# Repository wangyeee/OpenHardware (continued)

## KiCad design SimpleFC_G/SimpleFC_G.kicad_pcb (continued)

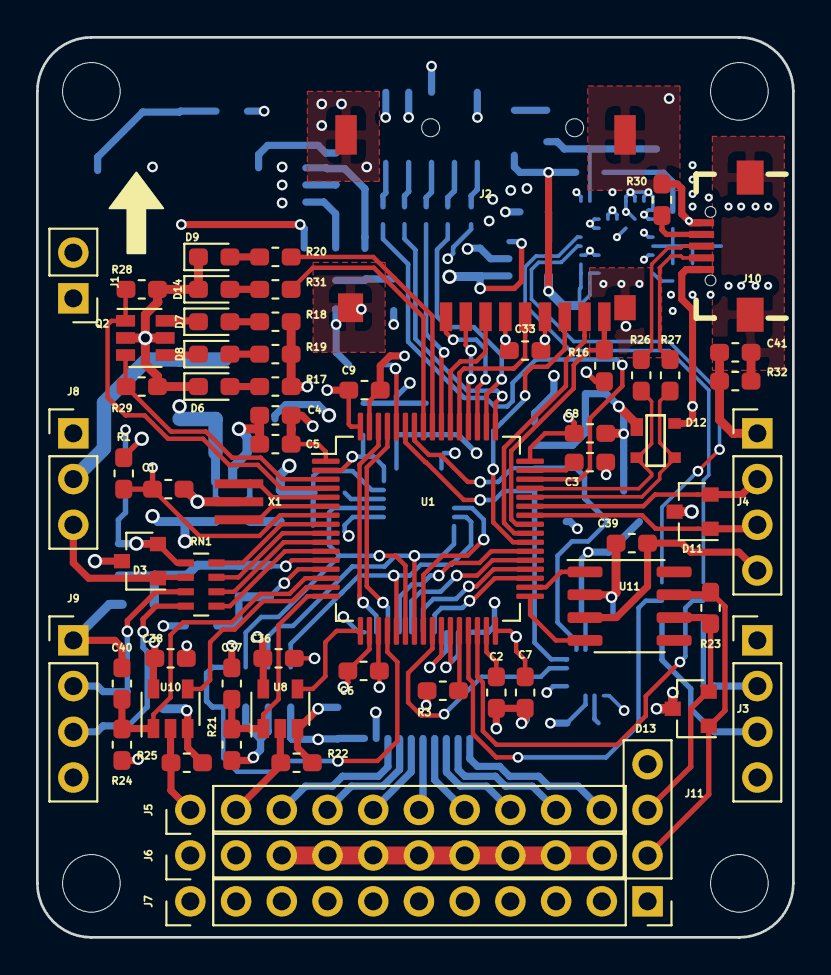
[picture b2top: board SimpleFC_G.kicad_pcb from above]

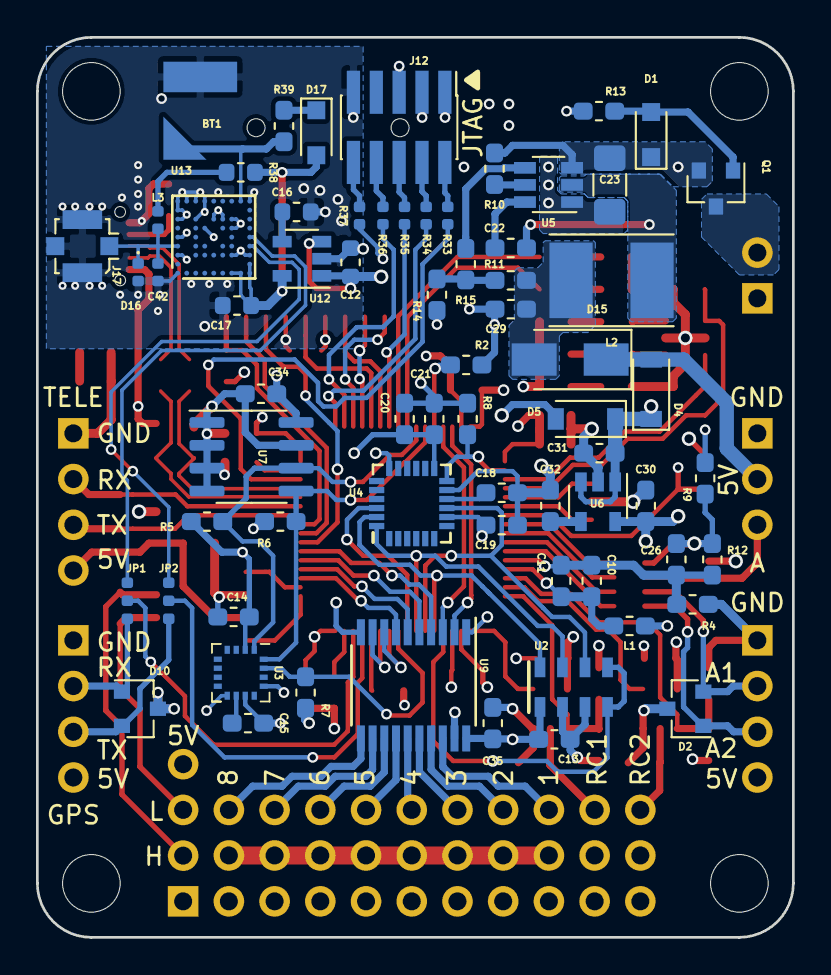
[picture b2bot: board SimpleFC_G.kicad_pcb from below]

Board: 4 copper layers, 42.0 x 50.0 mm, 134 parts (68 on the bottom side), 117 nets.

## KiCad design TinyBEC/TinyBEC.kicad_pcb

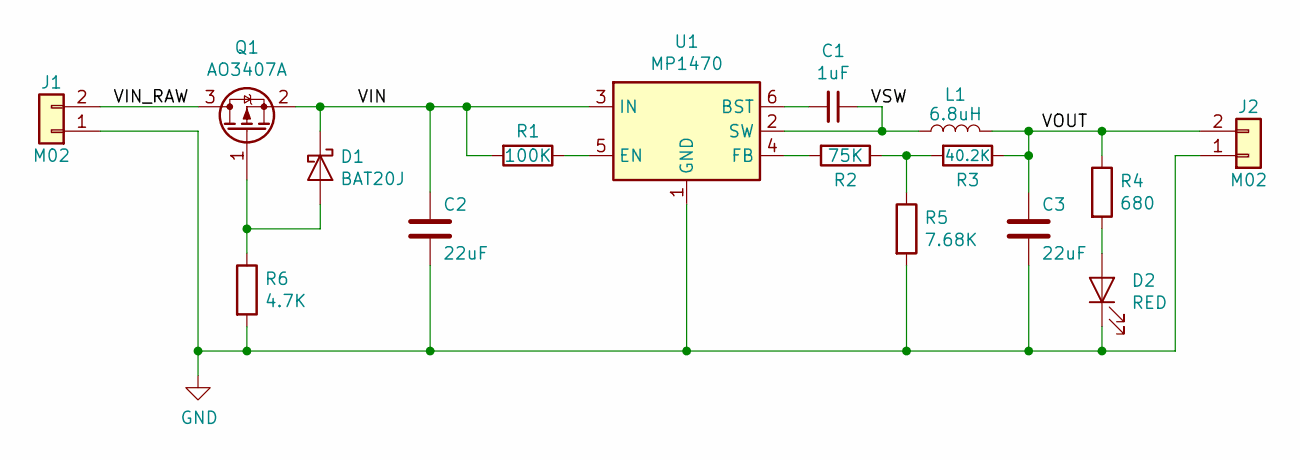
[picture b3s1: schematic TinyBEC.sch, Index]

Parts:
C1: 1uF; C_0603_1608Metric_Pad1.05x0.95mm_HandSolder
C2: 22uF; C_1812_4532Metric_Pad1.30x3.40mm_HandSolder
C3: 22uF; C_0805_2012Metric_Pad1.15x1.40mm_HandSolder
D1: BAT20J; D_SOD-123
D2: RED; LED_0603_1608Metric_Castellated
J1, J2: M02; PinHeader_1x02_P2.54mm_Vertical
L1: 6.8uH; L_Taiyo-Yuden_NR-50xx_HandSoldering
Q1: AO3407A; SOT-23
R1: 100K; R_0603_1608Metric_Pad1.05x0.95mm_HandSolder
R2: 75K; R_0603_1608Metric_Pad1.05x0.95mm_HandSolder
R3: 40.2K; R_0603_1608Metric_Pad1.05x0.95mm_HandSolder
R4: 680; R_0603_1608Metric_Pad1.05x0.95mm_HandSolder
R5: 7.68K; R_0603_1608Metric_Pad1.05x0.95mm_HandSolder
R6: 4.7K; R_0603_1608Metric_Pad1.05x0.95mm_HandSolder
U1: MP1470; TSOT-23-6

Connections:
/VIN: C2.1, D1.1 (K), Q1.2 (S), R1.2, U1.3 (IN)
/VIN_RAW: J1.2, Q1.3 (D)
/VOUT: C3.1, J2.2, L1.2, R3.1, R4.1
/VSW: C1.1, L1.1, U1.2 (SW)
GND: C2.2, C3.2, D2.1 (K), J1.1, J2.1, R5.2, R6.2, U1.1 (GND)
unnamed: C1.2, U1.6 (BST)
unnamed: D1.2 (A), Q1.1 (G), R6.1
unnamed: D2.2 (A), R4.2
unnamed: R1.1, U1.5 (EN)
unnamed: R2.1, R3.2, R5.1
unnamed: R2.2, U1.4 (FB)

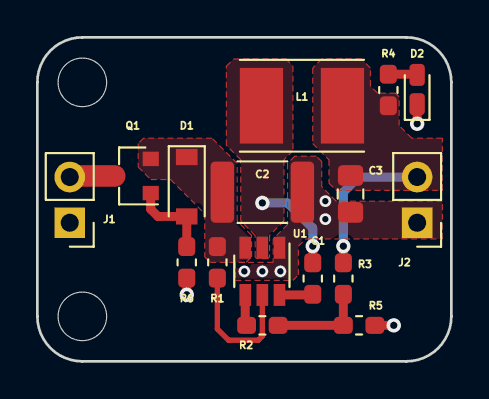
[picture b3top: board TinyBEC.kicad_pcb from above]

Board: 2 copper layers, 23.0 x 18.0 mm, 16 parts (0 on the bottom side), 11 nets.

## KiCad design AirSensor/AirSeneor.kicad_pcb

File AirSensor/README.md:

# Air Speed/Pressure Sensor
A barometer and differential pressure sensor board with CAN bus.

***WARNING: The PCB design has not been fabricated, Use with caution!***

## Hardware Design
### Main Components
1. [MS4525DO](https://www.te.com/usa-en/product-CAT-BLPS0002.html) differential pressure sensor.
2. [MS5611](https://www.te.com/usa-en/product-CAT-BLPS0036.html) air pressure sensor.
3. [STM32F072](https://www.st.com/en/microcontrollers-microprocessors/stm32f072cb.html) MCU.
4. [TJA1050](https://www.nxp.com/products/analog/interfaces/in-vehicle-network/can-transceiver-and-controllers/high-speed-can-transceiver:TJA1050) CAN bus transceiver.

## Software
The software is still work in progress. The following functionalities will be implemented.

1. Drivers barometer, differential pressure sensor and CAN bus.
2. Application layer supporting for [UAVCAN](https://uavcan.org/) protocol.

## 3D rendering

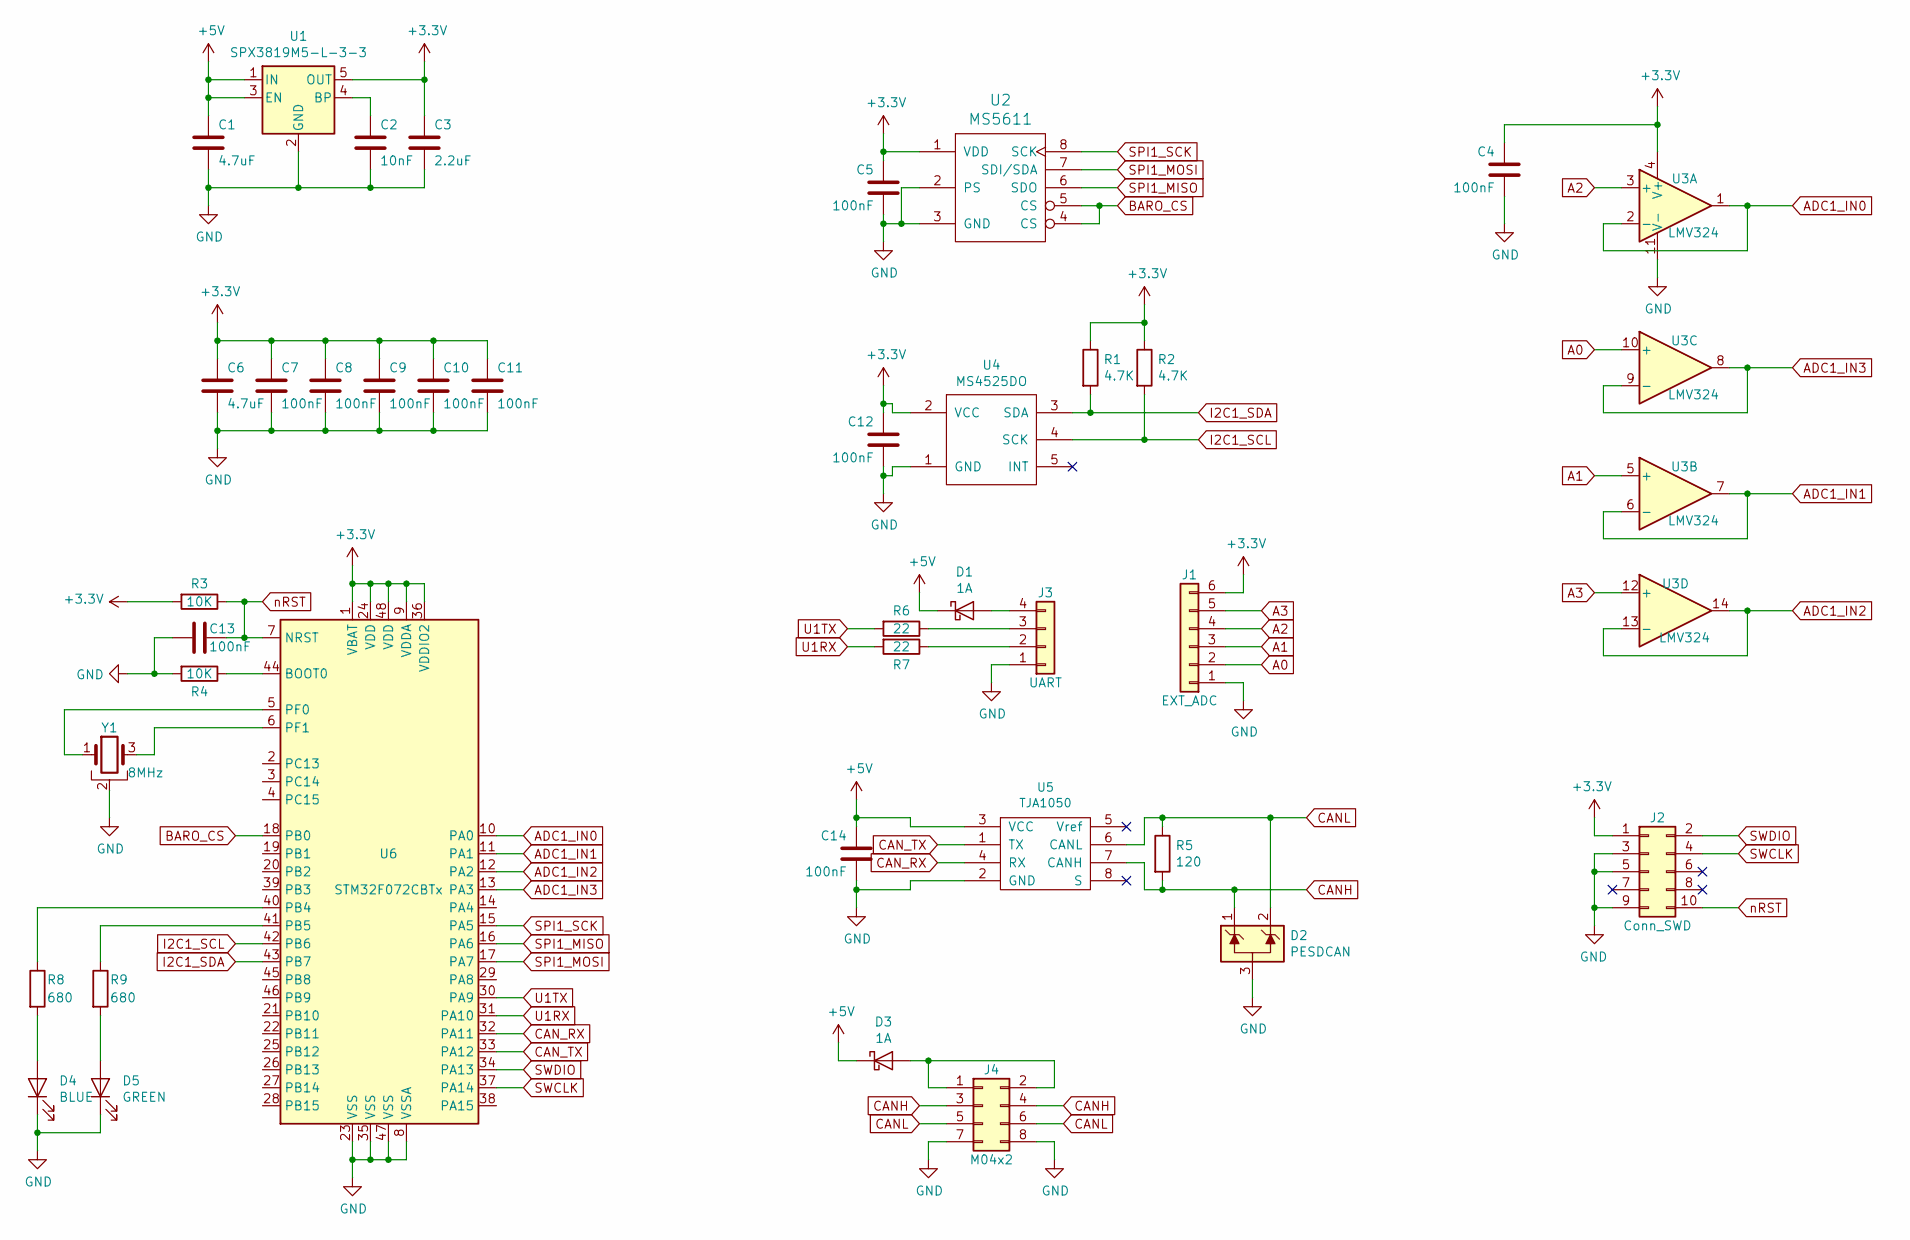
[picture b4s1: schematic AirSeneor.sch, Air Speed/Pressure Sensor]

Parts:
C1, C6: 4.7uF; C_0603_1608Metric
C2: 10nF; C_0603_1608Metric
C3: 2.2uF; C_0603_1608Metric
C4, C5, C7, C8, C9, C10, C11, C12, C13, C14: 100nF; C_0603_1608Metric
D1, D3: 1A; D_SOD-123
D2: PESDCAN; SOT-23
D4: BLUE; LED_0603_1608Metric
D5: GREEN; LED_0603_1608Metric
J1: EXT_ADC; PinHeader_1x06_P2.00mm_Vertical
J2: Conn_SWD; PinHeader_2x05_P1.27mm_Vertical_SMD
J3: UART; PinHeader_1x04_P2.54mm_Vertical
J4: M04x2; PinHeader_2x04_P2.54mm_Horizontal
R1, R2: 4.7K; R_0603_1608Metric
R3, R4: 10K; R_0603_1608Metric
R5: 120; R_0603_1608Metric
R6, R7: 22; R_0603_1608Metric
R8, R9: 680; R_0603_1608Metric
U1: SPX3819M5-L-3-3; SOT-23-5
U2: MS5611; LGA-8_3x5mm_P1.25mm
U3: LMV324; SOIC-14_3.9x8.7mm_P1.27mm
U4: MS4525DO; MS4525DO-DS
U5: TJA1050; SOIC-8_3.9x4.9mm_P1.27mm
U6: STM32F072CBTx; LQFP-48_7x7mm_P0.5mm
Y1: 8MHz; CERALOCK-CSTCE

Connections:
+3V3: C3.1, C4.1, C5.1, C6.1, C7.1, C8.1, C9.1, C10.1, C11.1, C12.1, J1.6, J2.1, R1.1, R2.1, R3.2, U1.5 (OUT), U2.1 (VDD), U3.4 (V+), U4.2 (VCC), U6.1 (VBAT), U6.9 (VDDA), U6.24 (VDD), U6.36 (VDDIO2), U6.48 (VDD)
+5V: C1.1, C14.1, D1.1 (K), D3.1 (K), U1.1 (IN), U1.3 (EN), U5.3 (VCC)
A0: J1.2, U3.10 (+)
A1: J1.3, U3.5 (+)
A2: J1.4, U3.3 (+)
A3: J1.5, U3.12 (+)
ADC1_IN0: U3.1, U3.2 (-), U6.10 (PA0)
ADC1_IN1: U3.6 (-), U3.7, U6.11 (PA1)
ADC1_IN2: U3.13 (-), U3.14, U6.12 (PA2)
ADC1_IN3: U3.8, U3.9 (-), U6.13 (PA3)
BARO_CS: U2.4 (CS), U2.5 (CS), U6.18 (PB0)
CANH: D2.1 (K), J4.3, J4.4, R5.2, U5.7 (CANH)
CANL: D2.2 (K), J4.5, J4.6, R5.1, U5.6 (CANL)
CAN_RX: U5.4 (RX), U6.32 (PA11)
CAN_TX: U5.1 (TX), U6.33 (PA12)
GND: C1.2, C2.2, C3.2, C4.2, C5.2, C6.2, C7.2, C8.2, C9.2, C10.2, C11.2, C12.2, C13.2, C14.2, D2.3 (A), D4.1 (K), D5.1 (K), J1.1, J2.3, J2.5, J2.9, J3.1, J4.7, J4.8, R4.2, U1.2 (GND), U2.2 (PS), U2.3 (GND), U3.11 (V-), U4.1 (GND), U5.2 (GND), U6.8 (VSSA), U6.23 (VSS), U6.35 (VSS), U6.47 (VSS), Y1.2
I2C1_SCL: R2.2, U4.4 (SCK), U6.42 (PB6)
I2C1_SDA: R1.2, U4.3 (SDA), U6.43 (PB7)
unnamed: C2.1, U1.4 (BP)
unnamed: D1.2 (A), J3.4
unnamed: D3.2 (A), J4.1, J4.2
unnamed: D4.2 (A), R8.2
unnamed: D5.2 (A), R9.2
unnamed: J3.2, R7.1
unnamed: J3.3, R6.1
unnamed: R4.1, U6.44 (BOOT0)
unnamed: R8.1, U6.40 (PB4)
unnamed: R9.1, U6.41 (PB5)
unnamed: U6.5 (PF0), Y1.1
unnamed: U6.6 (PF1), Y1.3
SPI1_MISO: U2.6 (SDO), U6.16 (PA6)
SPI1_MOSI: U2.7 (SDI/SDA), U6.17 (PA7)
SPI1_SCK: U2.8 (SCK), U6.15 (PA5)
SWCLK: J2.4, U6.37 (PA14)
SWDIO: J2.2, U6.34 (PA13)
U1RX: R7.2, U6.31 (PA10)
U1TX: R6.2, U6.30 (PA9)
nRST: C13.1, J2.10, R3.1, U6.7 (NRST)

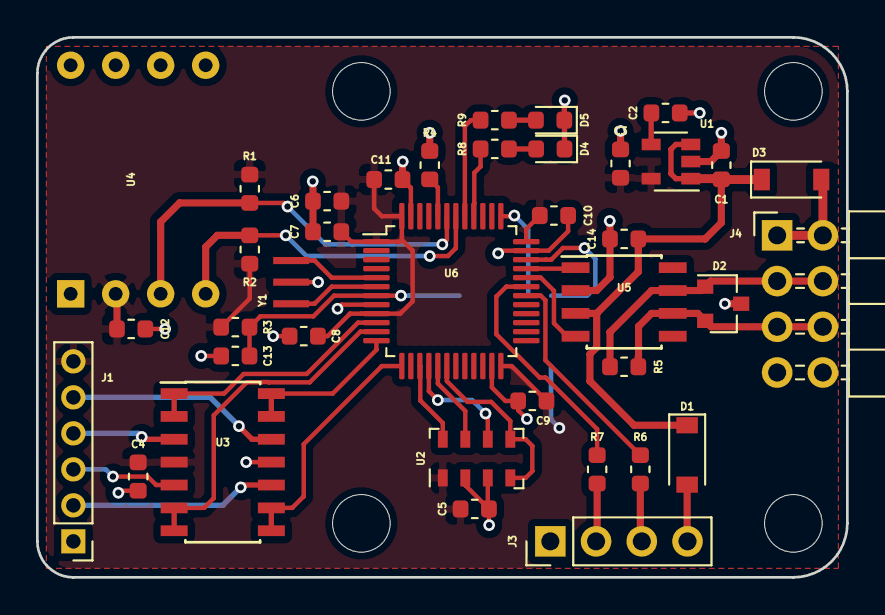
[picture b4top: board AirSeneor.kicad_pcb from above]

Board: 2 copper layers, 45.0 x 30.0 mm, 39 parts (1 on the bottom side), 38 nets.

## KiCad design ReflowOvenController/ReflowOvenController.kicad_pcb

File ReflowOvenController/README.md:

# Reflow Oven Controller
A reflow oven controller derived from [0xPIT/reflowOvenController](https://github.com/0xPIT/reflowOvenController).

**Warning: Lethal mains voltage is connected to the PCB, extreme care must be taken for the whole time. Seek help from professional technicians whenever possible.**

I decide to design my own board mainly because the solid state relay used in the original project is obsolete. In order to avoid this, I use a triac and an optocoupler to build a solid state relay. It's much easier to find alternatives for discrete components than integrate ones.

Another change from the original design is using ATmega328P to replace ATmega32U4 used in Arduino Pro Micro, this is simply because I already have some ATmega328P chips available. Note that due to this change, the Timer3 library is not available on this hardware.

### 3D preview

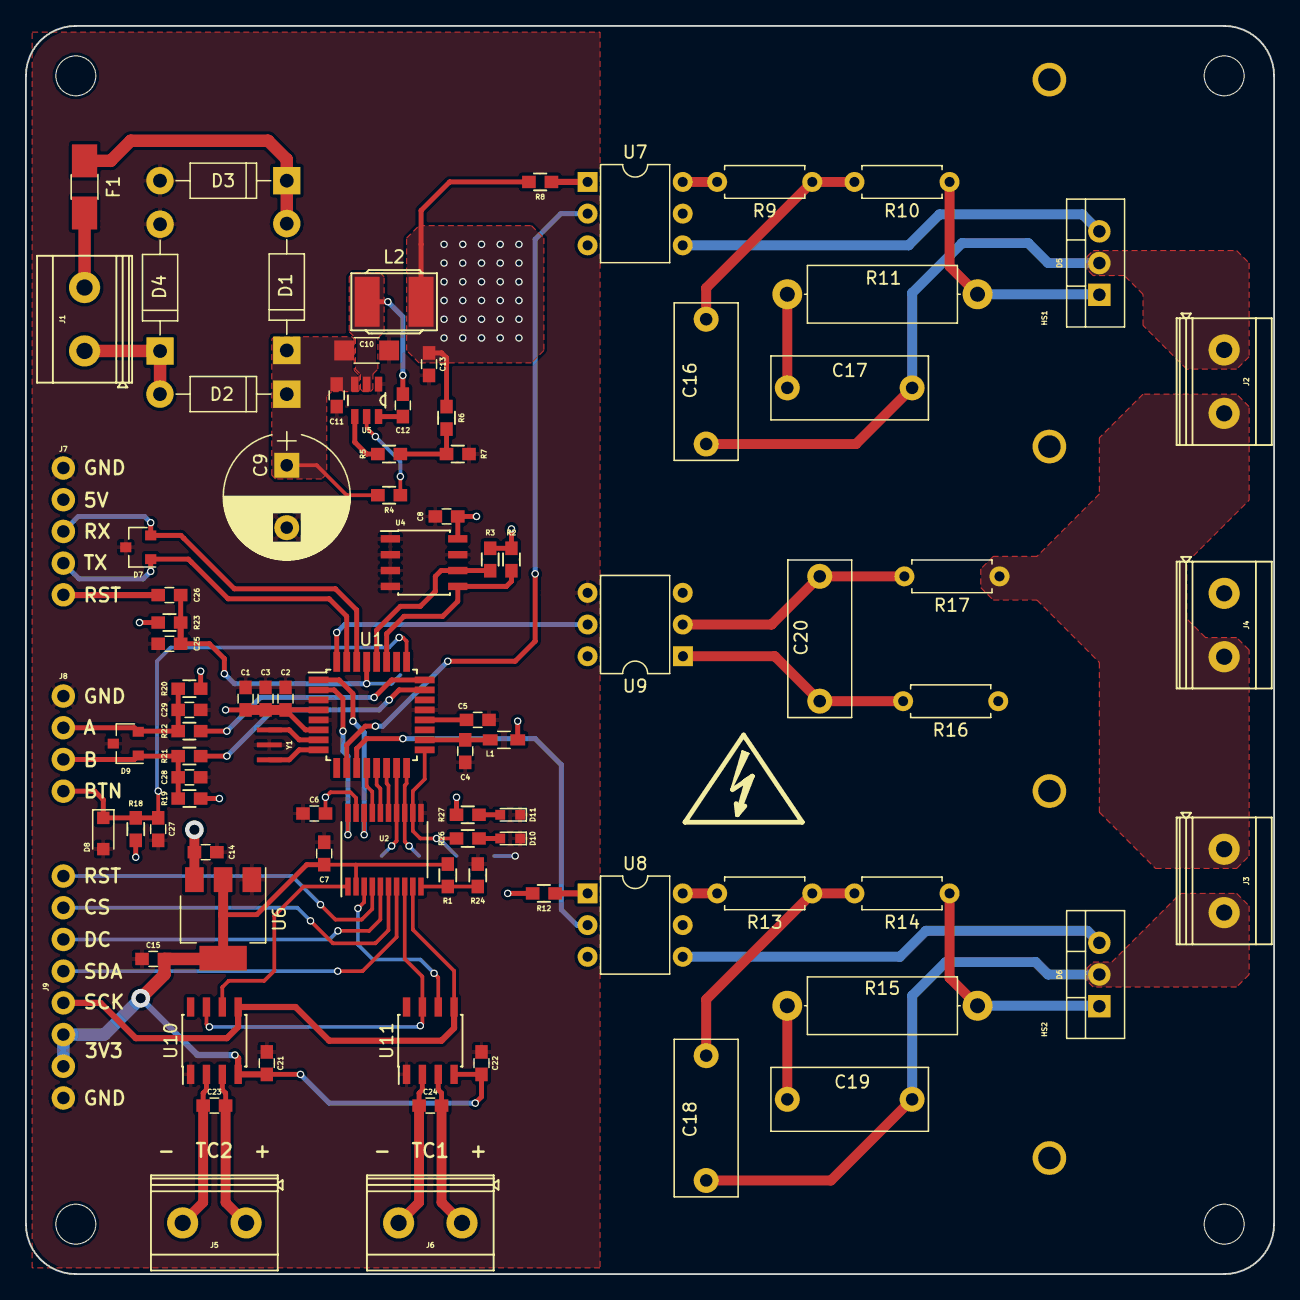
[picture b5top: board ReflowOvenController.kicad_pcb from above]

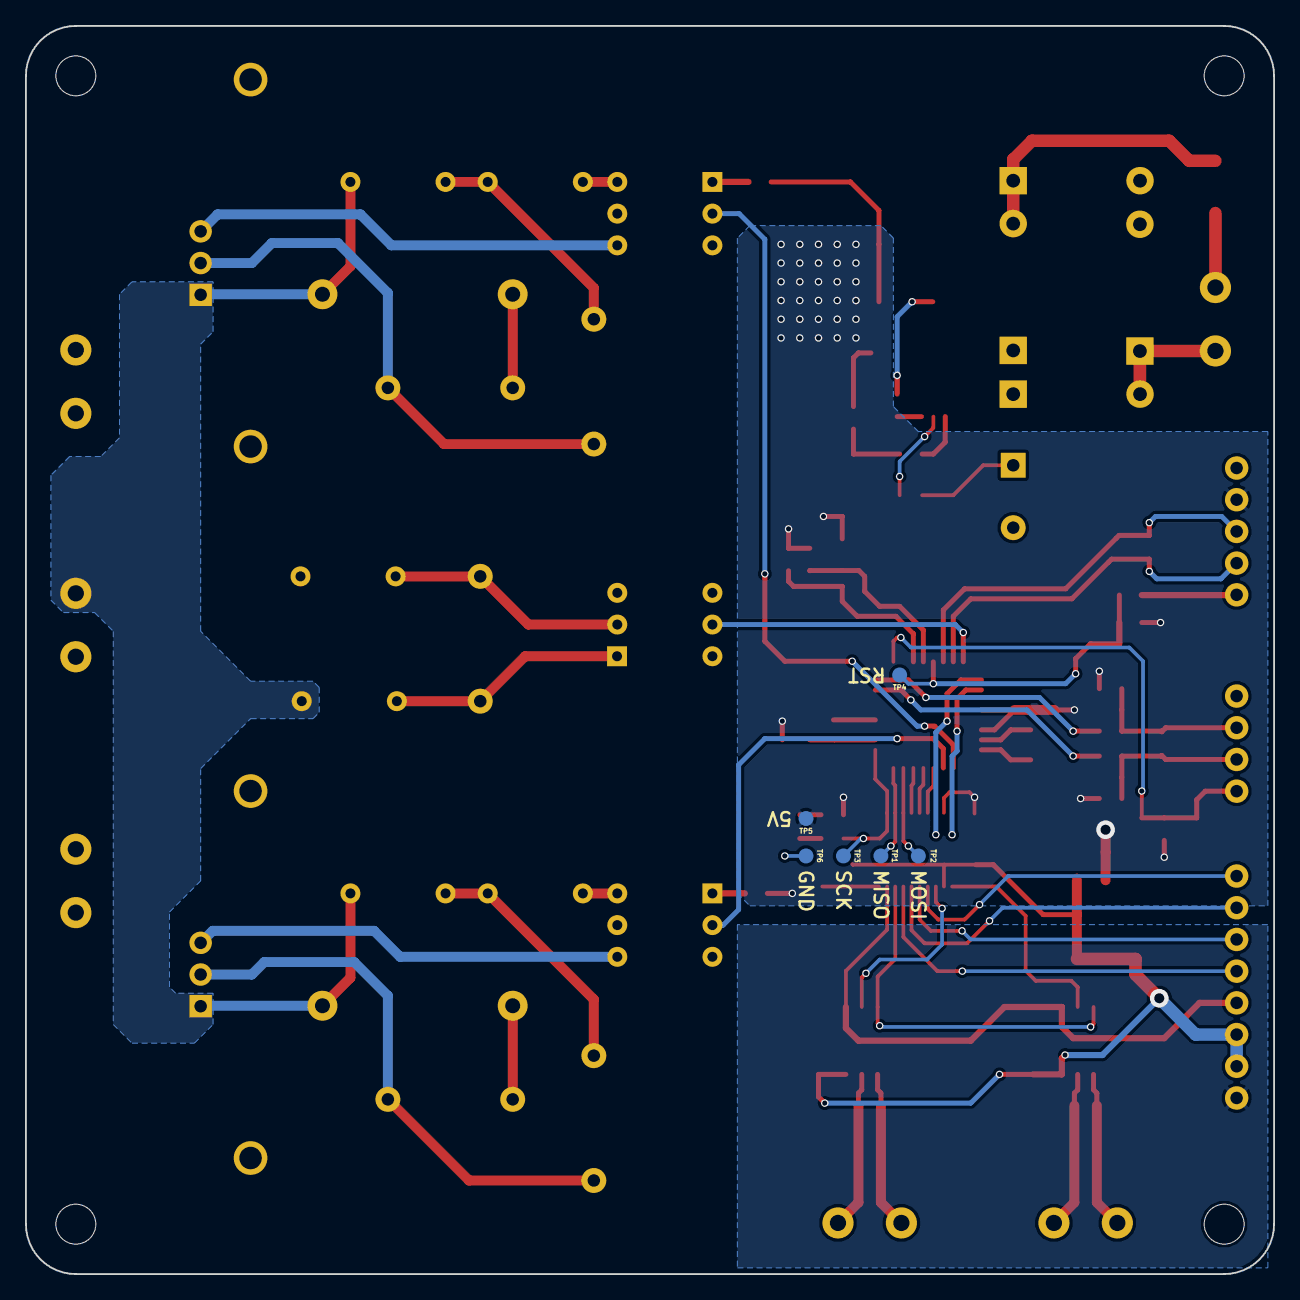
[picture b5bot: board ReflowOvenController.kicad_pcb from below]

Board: 2 copper layers, 100.0 x 100.0 mm, 102 parts (6 on the bottom side), 69 nets.

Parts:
C1: 4.7uF; C_0603_HandSoldering
C2, C3, C4, C5, C6, C7, C8, C11, C21, C22: 100nF; C_0603_HandSoldering
C9: 470uF; CP_Radial_D10.0mm_P5.00mm
C10: 22uF; C_1206_HandSoldering
C12, C14, C15: 1uF; C_0603_HandSoldering
C13: 22uF; C_0603_HandSoldering
C16, C18: 50nF; C_Disc_D12.5mm_W5.0mm_P10.00mm
C17, C19: 10nF; C_Disc_D12.5mm_W5.0mm_P10.00mm
C20: 100nF; C_Disc_D12.5mm_W5.0mm_P10.00mm
C23, C24, C27, C28, C29: 10nF; C_0603_HandSoldering
C25: NC; C_0603_HandSoldering
C26: 4.7nF; C_0603_HandSoldering
D1, D2, D3, D4: 1N4001; D_DO-41_SOD81_P10.16mm_Horizontal
D5, D6: BTA16; TO-220_Vertical
D7, D9: PESD5V; SOT-23
D8: PESD5V; D_SOD-323_HandSoldering
D10: GREEN; LED_0603
D11: RED; LED_0603
F1: 1A; Fuse_SMD1206_HandSoldering
HS1, HS2: XSD1226-362
HV: Symbol_HighVoltage_Type2_SlikTop_VerySmall; Symbol_HighVoltage_Type2_SilkTop_VerySmall
J1, J5, J6: CONN_01X02; MKDS3-2-5.08
J2: HEATER; MKDS3-2-5.08
J3: FAN; MKDS3-2-5.08
J4: MAIN; MKDS3-2-5.08
J7: M05
J8: M04
J9: M08
L1: 1K; L_0603_HandSoldering
L2: 6.8uH; Choke_SMD_Taiyo_NRS50XX-Handsoldering
M1, M2, M3, M4: M3; MountingHole_3.2mm_M3
R1, R2, R3: 4.7K; R_0603_HandSoldering
R4: 100K; R_0603_HandSoldering
R5: 75K; R_0603_HandSoldering
R6: 40.2K; R_0603_HandSoldering
R7: 7.68K; R_0603_HandSoldering
R8, R12, R21, R22: 100; R_0603_HandSoldering
R9, R13: 360; R_Axial_DIN0207_L6.3mm_D2.5mm_P7.62mm_Horizontal
R10, R14: 470; R_Axial_DIN0207_L6.3mm_D2.5mm_P7.62mm_Horizontal
R11, R15: 39; R_Axial_DIN0414_L11.9mm_D4.5mm_P15.24mm_Horizontal
R16, R17: 47K; R_Axial_DIN0207_L6.3mm_D2.5mm_P7.62mm_Horizontal
R18, R19, R20, R23: 10K; R_0603_HandSoldering
R24: NC; R_0603_HandSoldering
R26, R27: 330; R_0603_HandSoldering
TP1, TP2, TP3, TP4, TP5, TP6: TEST; TESTPAD_SMALL
U1: ATMEGA328P-AU; TQFP-32_7x7mm_Pitch0.8mm
U2: TXS0108E; TSSOP-20_4.4x6.5mm_Pitch0.65mm
U4: AT24CS512; SOIC-8_3.9x4.9mm_Pitch1.27mm
U5: MP1470; TSOT23-6
U6: LM1117-3.3; SOT-223
U7, U8: MOC3020M; DIP-6_W7.62mm
U9: H11A1M; DIP-6_W7.62mm
U10, U11: MAX31855; SOIC-8_3.9x4.9mm_Pitch1.27mm
Y1: 16MHz; CERALOCK-CSTCE

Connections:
+3V3: C7.1, C15.2, C21.2, C22.2, J9.2, J9.3, R1.1, U2.2, U6.2, U6.4, U10.4, U11.4
+5V: C1.1, C2.1, C3.1, C6.2, C8.2, C13.1, C14.2, J7.2, L1.1, L2.2, R2.1, R3.1, R6.1, R8.2, R12.2, R18.2, R19.2, R20.2, R23.1, R27.2, TP5.1, U1.4, U1.6, U2.19, U4.8, U6.3
+5VA: C4.1, L1.2, U1.18
DCDC_VIN: C9.1, C10.1, C11.1, D1.1, D2.1, R4.2, U5.3
ENC1: R21.2, U1.23
ENC2: R22.2, U1.24
ENC_BTN: C27.1, D8.1, J8.1, R18.1, U1.25
GND: C1.2, C2.2, C3.2, C4.2, C5.2, C6.1, C7.2, C8.1, C9.2, C10.2, C11.2, C13.2, C14.1, C15.1, C21.1, C22.1, C25.2, C27.2, C28.2, C29.2, D3.2, D4.2, D7.3, D8.2, D9.3, D10.1, D11.1, J7.1, J8.4, J9.1, R7.1, R24.1, TP6.1, U1.3, U1.5, U1.21, U2.11, U4.1, U4.2, U4.3, U4.4, U4.7, U5.1, U6.1, U9.4, U10.1, U11.1, Y1.2
LCD_CS: U1.14, U2.15
LCD_CS_3V3: J9.7, U2.6
LCD_DC: U1.13, U2.16
LCD_DC_3V3: J9.6, U2.5
LCD_RST: U1.12, U2.17
LCD_RST_3V3: J9.8, U2.4
LIVE: D5.1, D6.1, J4.1, R10.1, R11.2, R14.1, R15.2, R16.1
MISO: TP1.1, U1.16, U2.13
MISO_3V3: U2.8, U10.7, U11.7
MOSI: TP2.1, U1.15, U2.14
MOSI_3V3: J9.5, U2.7
NEUTRAL: J2.2, J3.1, J4.2, R17.1
unnamed: C5.1, U1.20
unnamed: C12.1, U5.6
unnamed: C16.1, R9.1, R10.2
unnamed: C17.1, R11.1
unnamed: C18.1, R13.1, R14.2
unnamed: C19.1, R15.1
unnamed: C20.1, R16.2, U9.1
unnamed: C20.2, R17.2, U9.2
unnamed: C28.1, D9.1, J8.2, R19.1, R21.1
unnamed: C29.1, D9.2, J8.3, R20.1, R22.1
unnamed: D1.2, D3.1, F1.1
unnamed: D2.2, D4.1, J1.1
unnamed: D5.3, U7.4
unnamed: D6.3, U8.4
unnamed: D10.2, R26.1
unnamed: D11.2, R27.1
unnamed: F1.2, J1.2
unnamed: R1.2, R24.2, U2.10
unnamed: R4.1, U5.5
unnamed: R5.1, R6.2, R7.2
unnamed: R5.2, U5.4
unnamed: R8.1, U7.1
unnamed: R9.2, U7.6
unnamed: R12.1, U8.1
unnamed: R13.2, U8.6
unnamed: U1.7, Y1.3
unnamed: U1.8, Y1.1
RESET: C25.1, C26.1, R23.2, TP4.1, U1.29
RST: C26.2, J7.5
RX: D7.2, J7.3, U1.30
SCK: R26.2, TP3.1, U1.17, U2.12
SCK_3V3: J9.4, U2.9, U10.5, U11.5
SCL: R3.2, U1.28, U4.6
SDA: R2.2, U1.27, U4.5
SSR1: U1.10, U7.2
SSR2: U1.11, U8.2
SSR_OUT1: C16.2, C17.2, D5.2, J2.1
SSR_OUT2: C18.2, C19.2, D6.2, J3.2
TC1+: C24.2, J6.1, U11.3
TC1-: C24.1, J6.2, U11.2
TC1_CS: U1.1, U2.18
TC1_CS_3V3: U2.3, U11.6
TC2+: C23.2, J5.1, U10.3
TC2-: C23.1, J5.2, U10.2
TC2_CS: U1.2, U2.20
TC2_CS_3V3: U2.1, U10.6
TX: D7.1, J7.4, U1.31
V_SW: C12.2, L2.1, U5.2
ZEROX: U1.32, U9.5

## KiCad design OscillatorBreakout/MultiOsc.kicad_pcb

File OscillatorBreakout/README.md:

# Oscillator Breakout
A simple breakout board for oscillators. It can be populated with either DIP-14, DIP-8 or 3225 package of oscillators.

## Assembly instructions

### Power supply

| Oscillator power voltage | Parts to populate |
|-------|-----------------|
| 5V | L1 |
| 3.3V or less | C1, C2, C3 and U1 |

### Package
C4 is only needed for 3225 SMD package oscillator, it can't be populated for any DIP package.

## 3D preview
### DIP-14 package

### DIP-8 package

### 3225 package

## Assembled board
Here is an assembled board with 25 MHz TCXO, no onboard LDO, and DC coupled.

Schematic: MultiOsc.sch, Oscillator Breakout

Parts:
C1, C4: 100nF; C_0603_HandSoldering
C2: 10nF; C_0603_HandSoldering
C3: 2.2uF; C_0603_HandSoldering
J1: SMA_EDGE
J2: M03
L1: DNP; R_0603_HandSoldering
R1: 0; R_0402
U1: TPS79333; SOT-23-5
X1: CXO_DIP14; Oscillator_DIP-14
X2: CXO_DIP8; Oscillator_DIP-8
X3: CXO_3225; Oscillator_SMD_SeikoEpson_SG8002CE-4Pin_3.2x2.5mm_HandSolde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

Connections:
+3V3: C3.1, C4.2, L1.2, U1.5 (OUT), X1.14, X2.8, X3.4
+5V: C1.1, J2.1, L1.1, U1.1 (IN), U1.3 (EN)
/CTRL: J2.3, X1.1, X2.1, X3.1
GND: C1.2, C2.2, C3.2, C4.1, J1.2, J2.2, U1.2 (GND), X1.7, X2.4, X3.2
unnamed: C2.1, U1.4 (BP)
unnamed: J1.1, R1.1
unnamed: R1.2, X1.8, X2.5, X3.3

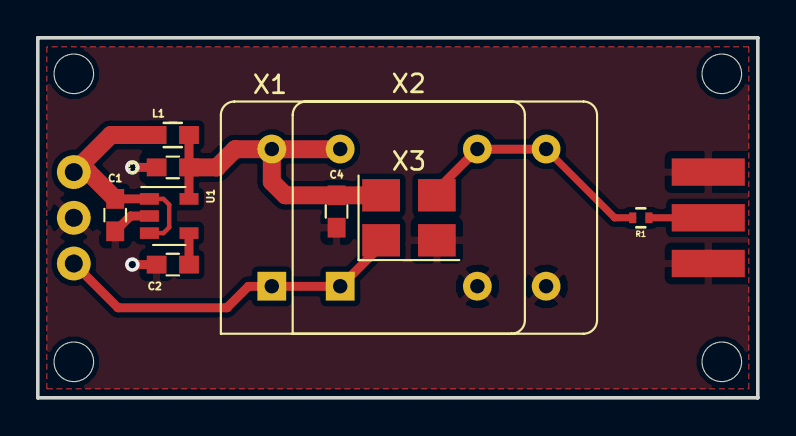
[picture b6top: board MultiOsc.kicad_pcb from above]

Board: 2 copper layers, 40.0 x 20.0 mm, 12 parts (0 on the bottom side), 7 nets.

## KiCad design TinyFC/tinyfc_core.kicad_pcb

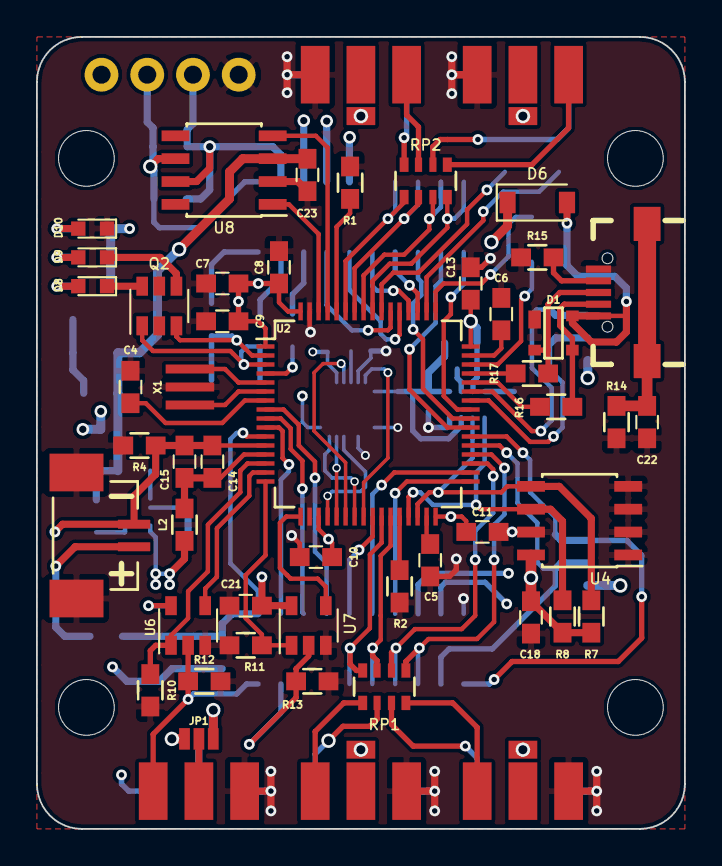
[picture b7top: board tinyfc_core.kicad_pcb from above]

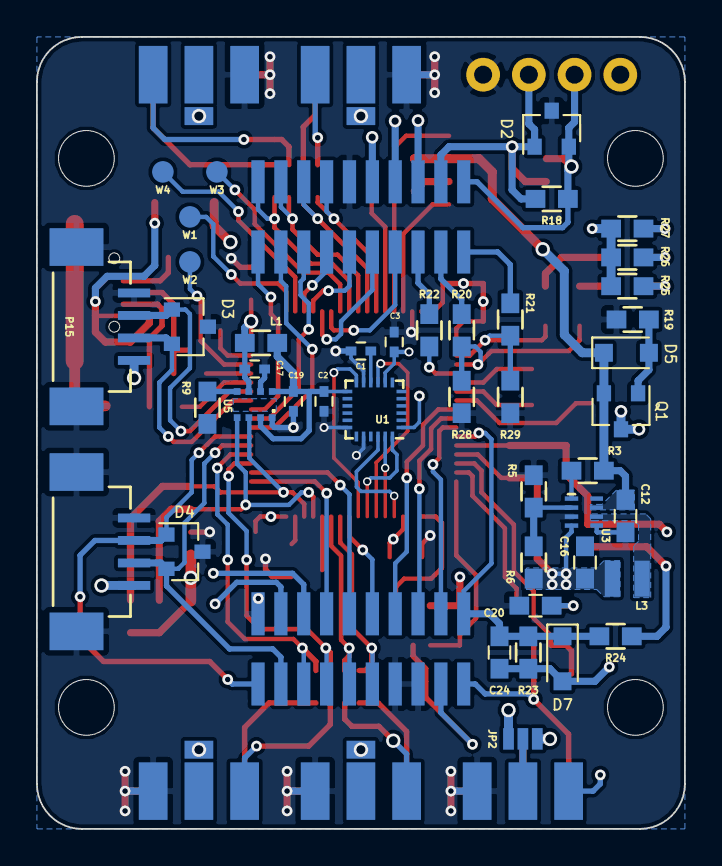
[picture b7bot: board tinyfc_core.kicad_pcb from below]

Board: 4 copper layers, 36.0 x 44.0 mm, 103 parts (50 on the bottom side), 96 nets.

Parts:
C1, C2, C17, C19: 100nF; C_0402
C3: 10nF; C_0402
C4, C8, C9, C10, C11, C13, C14, C18, C20, C21, C22, C23, C24: 100nF; C_0603_HandSoldering
C5, C6: 2.2uF; C_0603_HandSoldering
C7: 4.7uF; C_0603_HandSoldering
C12, C16: 10uF; C_0603_HandSoldering
C15: 1uF; C_0603_HandSoldering
D1: PRTR5V0U2X; SOT143B
D2: PESDCAN; SOT-23
D3, D4: PESD3V3; SOT-23
D5: BAT20J; D_SOD-323_HandSoldering
D6: 1A; D_SOD-123
D7: PESD3V3; D_SOD-323_HandSoldering
D8: GREEN; LED_0603
D9: BLUE; LED_0603
D10: RED; LED_0603
JP1, JP2: JUMPER3; JUMPER_DUAL_SMALL
L1, L2: 1K; R_0603_HandSoldering
L3: 1.5uH; VLS2520
MNT1: MOUNT_HOLES_OP
P1, P2: CONN_02X10; SMD2x10_1.27mm
P3, P4, P5, P6, P7, P8, P9, P10: CONN_01X03; M03_SMD-JP
P11, P12: CONN_01X03; M03_SMD
P13: USB-AB; USB-AB-MICRO
P14: CONN_01X04; M04
P15, P16: CONN_01X06; M04-1.25T
P17: CONN_01X04; M02-1.25T
Q1: Q_PMOS_GSD; SOT-23
Q2: AO6802; SOT-23-6
R1, R2, R10, R11, R12, R13, R24: 10K; R_0603_HandSoldering
R3, R6: 200K; R_0603_HandSoldering
R4: 0; R_0603_HandSoldering
R5: 44.2K; R_0603_HandSoldering
R7, R8, R19: 4.7K; R_0603_HandSoldering
R9, R15: 100K; R_0603_HandSoldering
R14: 1M; R_0603_HandSoldering
R16, R17, R20, R21, R22: 22; R_0603_HandSoldering
R18: 120; R_0603_HandSoldering
R23: 1K; R_0603_HandSoldering
R25, R26, R27: 470; R_0603_HandSoldering
R28, R29: 2.2K; R_0603_HandSoldering
RP1, RP2: 100; R_Array_Convex_4x0603
U1: MPU9250; QFN-24_3x3mm_Pitch0.4mm_NoMask
U2: STM32F405RGTx; LQFP-64_10x10mm_Pitch0.5mm
U3: MP2162; QFN8_2x1.5
U4: AT24C512C-SSHD; SOIC-8_3.9x4.9mm_Pitch1.27mm
U5: DPS310; PG-VLGA-8-1
U6, U7: 74AHC1G86; SOT-23-5
U8: TJA1050; SOIC-8_3.9x4.9mm_Pitch1.27mm
W1, W2, W3, W4: TEST_1P; TESTPAD_SMALL
X1: 25MHz; CERALOCK-CSTCW

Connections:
+3.3VADC: C14.1, C15.1, L2.2, U2.13
+3V3: C3.1, C7.1, C8.1, C9.1, C10.1, C11.1, C13.1, C16.1, C17.1, C18.1, C20.1, C21.1, JP1.3, JP2.3, L1.1, L2.1, L3.2, R6.1, R7.1, R8.1, U1.1, U1.8, U2.1, U2.19, U2.32, U2.48, U2.64, U3.4, U4.8, U5.6, U6.5, U7.5
+5V: C12.1, C23.2, D5.1, D6.1, Q1.2, R3.2, U3.7, U8.3
ADC1_IN10: P2.8, U2.8
ADC1_IN11: P2.6, U2.9
ADC1_IN12: P2.4, U2.10
ADC1_IN13: C24.2, D7.1, P2.2, R23.1, R24.2, U2.11
CAN1_RX: U2.61, U8.4
CAN1_TX: U2.62, U8.1
CANH: D2.1, P1.4, P14.3, R18.2, U8.7
CANL: D2.2, P1.2, P14.2, R18.1, U8.6
DIN1: Q2.3, R21.2, R29.2, U2.2
DIN2: Q2.1, R20.2, R28.2, U2.3
DIN3: R22.2, U2.4
GND: C1.2, C2.2, C3.2, C4.1, C5.2, C6.2, C7.2, C8.2, C9.2, C10.2, C11.2, C12.2, C13.2, C16.2, C17.2, C18.2, C19.2, C20.2, C21.2, C22.1, C23.1, D1.1, D2.3, D3.3, D4.3, D10.1, P1.12, P2.5, P2.7, P2.20, P3.3, P4.3, P5.1, P6.1, P7.3, P8.3, P9.1, P10.1, P11.3, P12.1, P13.GND, P14.4, P15.4, P15.5, P15.6, P16.4, P16.5, P16.6, P17.3, P17.4, Q2.2, Q2.5, R1.2, R2.1, R4.2, R5.2, R9.1, R10.2, R11.2, R12.2, R13.2, R14.2, R15.1, R19.1, R28.1, R29.1, U1.11, U1.18, U1.20, U2.18, U2.63, U3.3, U3.5, U4.1, U4.2, U4.3, U4.4, U4.7, U5.1, U5.7, U6.3, U7.3, U8.2, X1.2
GNDA: C14.2, C15.2, C24.1, D7.2, P17.2, R4.1, R23.2, U2.12
IMU_3V3: C2.1, C19.1, L1.2, U1.13, U5.2, U5.8
IMU_CS: U1.22, U2.20
IMU_INT: U1.12, U2.24
IMU_MISO: U1.9, U2.22
IMU_MOSI: U1.24, U2.23
IMU_SCK: U1.23, U2.21
IMU_SCL: R8.2, U2.29, U4.6, U5.4
IMU_SDA: R7.2, U2.30, U4.5, U5.3
JTCK: U2.49, W1.1
JTDI: U2.50, W4.1
JTDO: U2.55, W3.1
JTMS: U2.46, W2.1
LED1: P2.10, U2.25
LED2: P2.14, U2.33
LED3: P2.12, U2.34
unnamed: C1.1, U1.10
unnamed: C4.2, U2.7
unnamed: C5.1, U2.31
unnamed: C6.1, U2.47
unnamed: C22.2, P13.SHLD, R14.1
unnamed: D1.2, P13.DP, R17.2
unnamed: D1.3, P13.DM, R16.2
unnamed: D5.2, Q1.1, R19.2
unnamed: D8.1, Q2.6
unnamed: D8.2, R25.1
unnamed: D9.1, Q2.4
unnamed: D9.2, R26.1
unnamed: D10.2, R27.1
unnamed: JP1.2, P11.2
unnamed: JP2.2, P12.2
unnamed: P1.1, R21.1
unnamed: P1.3, R20.1
unnamed: P1.5, R22.1
unnamed: P13.ID, R15.2
unnamed: P17.1, R24.1
unnamed: R1.1, U2.60
unnamed: R2.2, U2.28
unnamed: R3.1, U3.1
unnamed: R5.1, R6.2, U3.2
unnamed: R9.2, U5.5
unnamed: U2.5, X1.1
unnamed: U2.6, X1.3
PWM1: P3.1, RP1.1
PWM2: P4.1, RP1.4
PWM3: P5.3, RP1.2
PWM4: P6.3, RP1.3
PWM5: P7.1, RP2.3
PWM6: P8.1, RP2.1
PWM7: P9.3, RP2.4
PWM8: P10.3, RP2.2
RC1_RX: P2.1, P11.1, R12.1, U6.2
RC2_RX: P2.3, P12.3, R13.1, U7.2
SDIO_CK: P1.9, U2.53
SDIO_CMD: P1.7, U2.54
SDIO_D0: P1.17, U2.39
SDIO_D1: P1.15, U2.40
SDIO_D2: P1.13, U2.51
SDIO_D3: P1.11, U2.52
SD_DECT: P1.19, U2.41
T3C1: P1.20, RP2.8, U2.56
T3C2: P1.18, RP2.7, U2.57
T3C3: P2.9, RP1.8, U2.26
T3C4: P2.11, RP1.7, U2.27
T4C1: P1.16, RP2.6, U2.58
T4C2: P1.14, RP2.5, U2.59
T12C1: P2.13, RP1.6, U2.35
T12C2: P2.15, RP1.5, U2.36
U1RX: D3.1, P2.16, P15.3, U2.43
U1TX: D3.2, P2.18, P15.2, U2.42
U2RX: U2.17, U7.4
U2TX: R11.1, U2.16, U7.1
U4RX: U2.15, U6.4
U4TX: R10.1, U2.14, U6.1
U6RX: D4.1, P2.19, P16.3, U2.38
U6TX: D4.2, P2.17, P16.2, U2.37
USBDM: R16.1, U2.44
USBDP: R17.1, U2.45
USB_VBUS: D1.4, D6.2, P13.VBUS
VIN_RAW: JP1.1, JP2.1, P1.6, P1.8, P1.10, P3.2, P4.2, P5.2, P6.2, P7.2, P8.2, P9.2, P10.2, P14.1, P15.1, P16.1, Q1.3, R25.2, R26.2, R27.2
V_SW: L3.1, U3.6

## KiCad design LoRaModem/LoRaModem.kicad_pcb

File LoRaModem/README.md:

# LoRa Modem
A board with Ra-02 LoRa Module and STM32 MCU. It is designed as auxiliary telemetry unit for a drone. The typical use case is to send GPS locations when the drone is lost.

## Hardware Design
### Main Components
1. Ra-02 LoRa Module: This is a long distance modem made by [AI-thinker](http://wiki.ai-thinker.com/_media/lora/docs/c048ps01a1_ra-02_product_specification_v1.1.pdf). It's based on Semtech [SX1278](https://www.semtech.com/products/wireless-rf/lora-transceivers/SX1278) transceiver. The module also features an IPEX antenna which allows external antennas.
2. STM32 MCU: The main control logic runs on a [STM32F103CBT6](https://www.st.com/en/microcontrollers/stm32f103cb.html) chip.

### IO Connections
Here are summary of connections used, for details, refer to LoRaSTM32Cube.ioc in the repo, it can be viewed with [STM32CubeMX](https://www.st.com/en/development-tools/stm32cubemx.html).

1. Serial port (Full-duplex): This port connects to a dedicate GPS receiver, or it can read GPS messages from standard telemetry (such as MavLink) port from an autopilot.
2. CAN bus: This is used to talk to the autopilot, as well as other devices on the same bus. Currently there is no plan for software support.
3. Serial port (Half-duplex): This is a TX only serial port, with built-in inverter which can be used to generate S.Bus signals. It could be used to control external severos for custom purposes.
4. Flash memory: The onboard flash chip can be used to store information like device ID, as well as logs.

## Software
The majority part of software is still work in progress. The following tasks are currently planned.

1. Drivers for SX1278, serial ports, flash and CAN bus.
2. Data TX/RX via SX1278.
3. Data parser for NMEA, UBLOX, MavLink, etc.

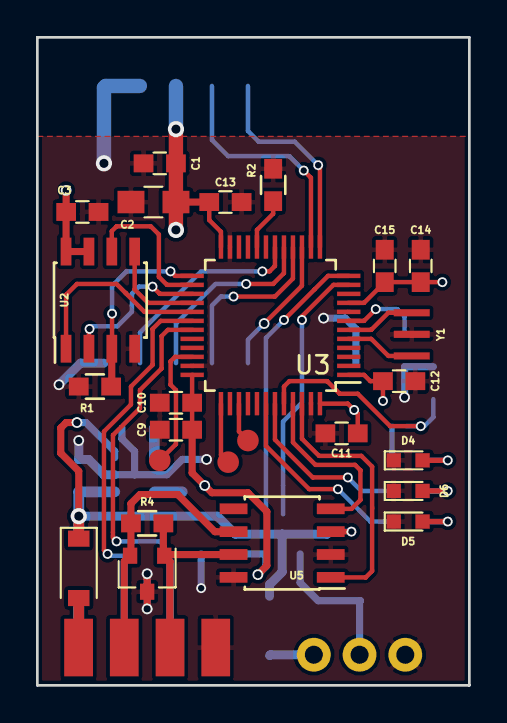
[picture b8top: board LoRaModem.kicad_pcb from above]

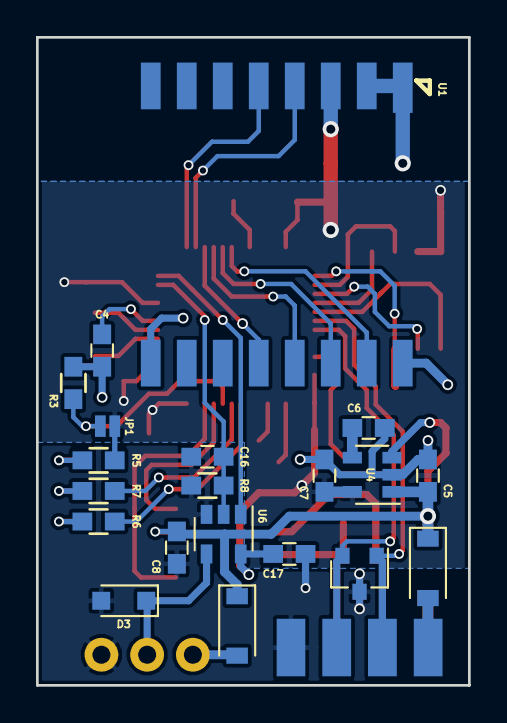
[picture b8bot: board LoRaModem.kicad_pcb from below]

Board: 2 copper layers, 24.0 x 36.0 mm, 48 parts (21 on the bottom side), 40 nets.

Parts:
C1, C3, C4, C8, C10, C11, C12, C13, C15, C17: 100nF; C_0603_HandSoldering
C2: 22uF; C_0805_HandSoldering
C5, C7: 2.2uF; C_0603_HandSoldering
C6, C16: 10nF; C_0603_HandSoldering
C9: 10uF; C_0603_HandSoldering
C14: 1uF; C_0603_HandSoldering
D1, D8, D9: 1A; D_SOD-123
D2: PESD3V3; SOT-23
D3: PESD3V3; D_SOD-323_HandSoldering
D4: RED; LED_0603
D5: BLUE; LED_0603
D6: GREEN; LED_0603
D7: PESDCAN; SOT-23
J1, J3: CONN_01X04; M04_SMD
J2: CONN_01X03; M03
JP1: Jumper; JUMPER_SMALL
R1: 47K; R_0603_HandSoldering
R2, R3: 10K; R_0603_HandSoldering
R4: 120; R_0603_HandSoldering
R5, R6, R7: 470; R_0603_HandSoldering
R8: 1.5K; R_0603_HandSoldering
TP1: SWDIO; TESTPAD_SMALL
TP2: SWCLK; TESTPAD_SMALL
TP3: SWO; TESTPAD_SMALL
U1: Ra-02; RA0x-LCC16
U2: W25X40; SOIC-8_3.9x4.9mm_Pitch1.27mm
U3: STM32F103CBTx; LQFP-48_7x7mm_Pitch0.5mm
U4: SPX3819; SOT-23-5
U5: TJA1050; SOIC-8_3.9x4.9mm_Pitch1.27mm
U6: 74AHC1G86; SOT-23-5
Y1: 8MHz; CERALOCK-CSTCE

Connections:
+3V3: C1.1, C2.1, C3.1, C7.1, C9.1, C10.1, C11.1, C12.1, C13.1, C14.1, C15.1, C17.2, JP1.1, R5.1, U1.3, U2.7, U2.8, U3.1, U3.9, U3.24, U3.36, U3.48, U4.5, U6.5
+5V: C5.1, C8.1, D1.1, D8.1, D9.1, U4.1, U4.3, U5.3
BOOT0: JP1.2, R3.1, U3.44
CANH: D7.1, J3.3, R4.2, U5.7
CANL: D7.2, J3.2, R4.1, U5.6
CANRX: U3.45, U5.4
CANTX: U3.46, U5.1
FLASH_CS: U2.1, U3.29
FLASH_WP: R1.2, U2.3, U3.25
GND: C1.2, C2.2, C3.2, C4.1, C5.2, C6.2, C7.2, C8.2, C9.2, C10.2, C11.2, C12.2, C13.2, C14.2, C15.2, C16.2, C17.1, D2.3, D3.2, D4.1, D5.1, D6.1, D7.3, J1.4, J2.3, J3.4, R1.1, R2.2, R3.2, R8.1, U1.1, U1.2, U1.9, U1.16, U2.4, U3.8, U3.23, U3.35, U3.47, U4.2, U5.2, U5.8, U6.3, Y1.2
LED1: R6.1, U3.42
LED2: R7.1, U3.43
LORA_CS: U1.15, U3.18
LORA_INT: U1.5, U3.13
LORA_RST: U1.4, U3.14
unnamed: C4.2, U3.7
unnamed: C6.1, U4.4
unnamed: D3.1, J2.2, U6.4
unnamed: D4.2, R5.2
unnamed: D5.2, R6.2
unnamed: D6.2, R7.2
unnamed: R2.1, U3.20
unnamed: U3.5, Y1.1
unnamed: U3.6, Y1.3
PWR_IN1: D1.2, J3.1
PWR_IN2: D8.2, J2.1
PWR_IN3: D9.2, J1.1
SB_INV: C16.1, R8.2, U3.11, U6.2
SPI1_MISO: U1.13, U3.16
SPI1_MOSI: U1.14, U3.17
SPI1_SCK: U1.12, U3.15
SPI2_MISO: U2.2, U3.27
SPI2_MOSI: U2.5, U3.28
SPI2_SCK: U2.6, U3.26
SWCLK: TP2.1, U3.37
SWDIO: TP1.1, U3.34
SWO: TP3.1, U3.39
U1RX: D2.2, J1.3, U3.31
U1TX: D2.1, J1.2, U3.30
U2TX: U3.12, U6.1

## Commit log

2016-02-22 Initial version. Including PowerModule and SerialBTBridge.
2016-02-28 Add multi rotor hub design files.
2016-06-13 Add ACS758 current sensor board.
2018-08-31 Add SimpleFC design files.
2018-09-28 Add design files for LoRa Modem.
2018-09-28 Add PDF schematics.
2018-09-28 Create LICENSE
2018-10-03 Add design files for TinyFC core board.
2018-10-07 Add design files for oscillator breakout board.
2018-10-07 Add 3D render for SimpleFC.
2018-10-09 Add description for each folder.
2018-10-27 Add files for ReflowOvenController
2019-01-03 Add STM32CubeMX design file for SimpleFC
2019-04-05 Import project AirSensor
2019-04-05 Add readme for AirSensor
2019-04-05 Update readme of AirSensor
2019-05-01 Add DIYDummyLoad EAGLE files
2019-05-01 Update README for DIYDummyLoad
2019-05-15 1. Replace SWD connector with 10 pin SMD 2x5 connector in AirSensor. 2. Add signal name silk screen in AirSensor.
2019-05-15 Update schematics and PCB print for AirSensor.
2019-05-17 Add version 2 of SimpleFC
2019-05-17 Add SimpleFCv2 schematics print and update README
2019-05-18 Replace MAG3110 with MMC5883MA in SimpleFC
2019-05-18 Update SimpleFCv2 README
2019-05-18 Update gitignore to include gerber drill files
2019-05-27 Add design files for TinyBEC
2019-05-27 Update README for TinyBEC
2019-06-04 Add design files for SimpleFCv2 with integrated GPS receiver
2019-06-04 Update README for SimpleFC_G
2020-01-29 Refactor SimpleFC schematics with latest KiCAD libraries.
